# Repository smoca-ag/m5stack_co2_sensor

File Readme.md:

# Build your own portable, graphing CO₂ sensor

## Motivation

CO₂ levels measured indoors can be used as an indicator of air quality.

Outdoor air has a CO₂ ppm level of 400 ppm. Humans exhale air with 40000 ppm. You can calculate the percentage of exhaust air you are breathing by dividing measured CO₂ level above outdoor by the human exhaust level. Used air might contain aerosols which might contain the corona virus.

High indoor CO₂ levels also have an impact on the cognitive performance of humans.

Smoca AG decided to build this easy to reproduce CO₂ measuring device to help slow the spread of the corona virus in offices.
It supports its users in deciding when ventilating the room begin monitored is advisable. It also raises awareness for the correlation between CO₂ level and air quality.

## Hardware

The following hardware is needed:

| description                 | cost     | link                                                                                                                             |
| --------------------------- | -------- | -------------------------------------------------------------------------------------------------------------------------------- |
| Sensirion SCD30             | 54 USD   | https://www.digikey.com/en/products/detail/sensirion-ag/SCD30/8445334<br>Switzerland: https://www.bastelgarage.ch/co2-sensor-scd30-sensirion                                                            |
| M5 Stack Core2              | 39.9 USD | https://www.digikey.com/en/products/detail/m5stack-technology-co-ltd/K010/13151126?s=N4IgTCBcDaILYFYDOAXAhgYwNYAIMHsAnAUwgF0BfIA<br>Switzerland: https://www.bastelgarage.ch/m5stack-core2-esp32-iot-entwicklungs-kit |
| M5 Stack Proto Board        | 2.95 USD | https://www.digikey.com/en/products/detail/m5stack-technology-co-ltd/M001/10492145<br>Switzerland: https://www.bastelgarage.ch/m5stack-core-development-proto-board                                               |
| M5 Stack PLC Base           | 9.95 USD | https://m5stack.com/collections/m5-base/products/plc-proto-industrial-board-module<br>Switzerland: https://www.bastelgarage.ch/m5stack-plc-proto-base-industrial-board                                               |
| M5 Stack Battery (optional) | 7.95 USD | https://www.digikey.com/en/products/detail/m5stack-technology-co-ltd/M002/10492127<br>Switzerland: https://www.bastelgarage.ch/m5stack-battery-module-700mah-fur-esp32-core                                               |

Note: The optional battery increases the battery operation time from 6 to 10 hours.

### Building

|Description | Image
|----------- | -----------
|1. Power the Core2 module. A factory test application should be loaded. Test the device. |
|2. Remove the bottom of the Core2 module. Keep the battery there or replace it with the optional bigger one. | 
|3. Remove the PCB from the proto module. |
|4. Connect the SCD30 module to the proto module. We used pin headers. | 
|5. Connect VDD with 3V3, GND with GND, TX/SCL with pin 5 and RX/SDA with pin 2. The other pins don't need to be connected to the proto module. | 
|5. Screw the proto module to the PLC Base |
|6. Screw the PLC Base to the Core2 module | 
|7. HW Done, load the software |

## Software

To initialise the device do the following:

1. Install [Platformio IDE](https://platformio.org/platformio-ide) or [PlatformIO Core](https://docs.platformio.org/en/latest/core/installation.html) to use another IDE
2. Open the `co2-sensor` project folder
3. Flash the `main.cpp` script to your M5 Stack Core2 with `pio run -t upload --upload-port {your_device}`. You can see a list of your devices with `pio device list`. Dependencies are installed automatically.

## Features

#### Calibration

The SCD30 can be calibrated manually or automatically. For manual calibration, the device must be placed outdoors for at least five minutes. Then the calibration can be adjusted. Fresh air has a CO₂ concentration of about 400 ppm. To use automatic calibration, the device must have access to fresh air for at least one hour a day.

#### WiFi

To use MQTT, synchronization and update functionality the device must have internet connection. To add WiFi credentials the device opens an access point with a web interface (Default IP is 192.168.4.1). 

#### Data sharing via MQTT

[MQTT](https://mqtt.org/) can be used to send the sensors data to a custom MQTT broker. Server, Port, Topic, Device name, Username and Password can also be configured in the web interface. Each minute the device sends its data in the following format: `{TOPIC}/{CATEGORY} {VALUE}`. Here an example: `sensor/co2 650`.  
Topics are able to have subtopics: `office2/meeting_room1/co2 1100`.  
The following categories are provided by the device: `/co2`, `/humidity`, `/temperature`.

#### Time synchronization

To keep time up to date the device synchronizes with a time server each night between two and three o'clock.

#### Firmware updates

Is a new firmware available, it can manually be updated via WiFi.

#### SNMP

Using SNMP you are able to read the values of the co2, temperature and humidity sensors and also check the battery status of the device:
1. First you have to make sure you have net-snmp installed on your system. You can do this using your package manager or by downloading it from http://www.net-snmp.org/download.html
2. Second you have to find out where your mib files are stored using the command ```net-snmp-config --default-mibdirs```.
3. Then you have to copy the [mib file](./snmp-mib/sensorhub.mib) from ```/snmp-mib/sensorhub.mib``` into one of the listed directories. e.g. ```cp snmp-mib/sensorhub.mib ~/.snmp/mibs```
4. Done that, you can now use snmptable to list the sensors: 
    ```snmptable -m +SENSORHUB-MIB -c public {IP-Address} shSensorTable```
    \
    Which should output the following:
    ```
    SNMP table: SENSORHUB-MIB::shSensorTable

    shSensorName
            SCD30
            BATTERY
   ```
    or to list the measurement values: 
    ```snmptable -m +SENSORHUB-MIB -c public {IP-Address} shMeasurementTable```
    \
    Which should output something like this:
    ```
    SNMP table: SENSORHUB-MIB::shMeasurementTable

    shMeasurementType shMeasurementValue
                co2                  617
        temperature                  207
           humidity                  433
            voltage                  3
    electricCurrent                  276
   ```

## Usage

**Disclaimer This is not a safety device. Always follow the local regulations regarding corona safety. No warranty is provided**

### Graphs

- The graphs alway show the last six hours. Every line on the graph represents the measurement of one minute. The last value measured in the given minute is used for the graph.
- To switch between different graphs (temperature / humidity / battery / co2) touch the corresponding value in the display

### microsd

If a microsd card formated with fat is present, a csv file, data.txt will be written every 2 seconds with the timestamp, the co2 level, the humidity, the temperature and the current battery charge.

### CO₂

| level           | color  | description                                                                                               |
| --------------- | ------ | --------------------------------------------------------------------------------------------------------- |
| < 600 ppm       | blue   | outdoor air                                                                                               |
| 600 - 800 ppm   | green  | fresh indoor air                                                                                          |
| 800 - 1000 ppm  | yellow | indoor air, ventilate the room if possible, small possibility of virus transmission                       |
| 1000 - 1400 ppm | orange | used indoor air, ventilate the room, cognition is impacted, possibility of virus transmission             |
| > 1400 ppm      | red    | heavy used indoor air, heavy cognition impact, high possiblity of virus transmission, ventilation needed. |

## Extended uses (no code provided)

- We use it at our office to control a couple of exhaust / inlet pwm computer fans to keep the CO₂ level below 800 ppm.
- We log the measurement results to a influxdb with a grafana dashboard. The grafana instance sends alerts to telegram for CO₂ levels above 800 ppm.

## SCD4x
There is a PCB in the PCB folder for SCD41 Support. The Code Supports transparently SCD40 and SCD30 at the moment.

## Contact

If you have any suggestions for the project feel free to file an issue. If you want to build the device on a bigger scale / have any other development / prototyping needs, feel free to contact us: info@smoca.ch

## License

Copyright (c) 2020 David Gunzinger / smoca AG www.smoca.ch \
Code: GPL v3 \
Text / Graphics / Photographs: CC BY-SA

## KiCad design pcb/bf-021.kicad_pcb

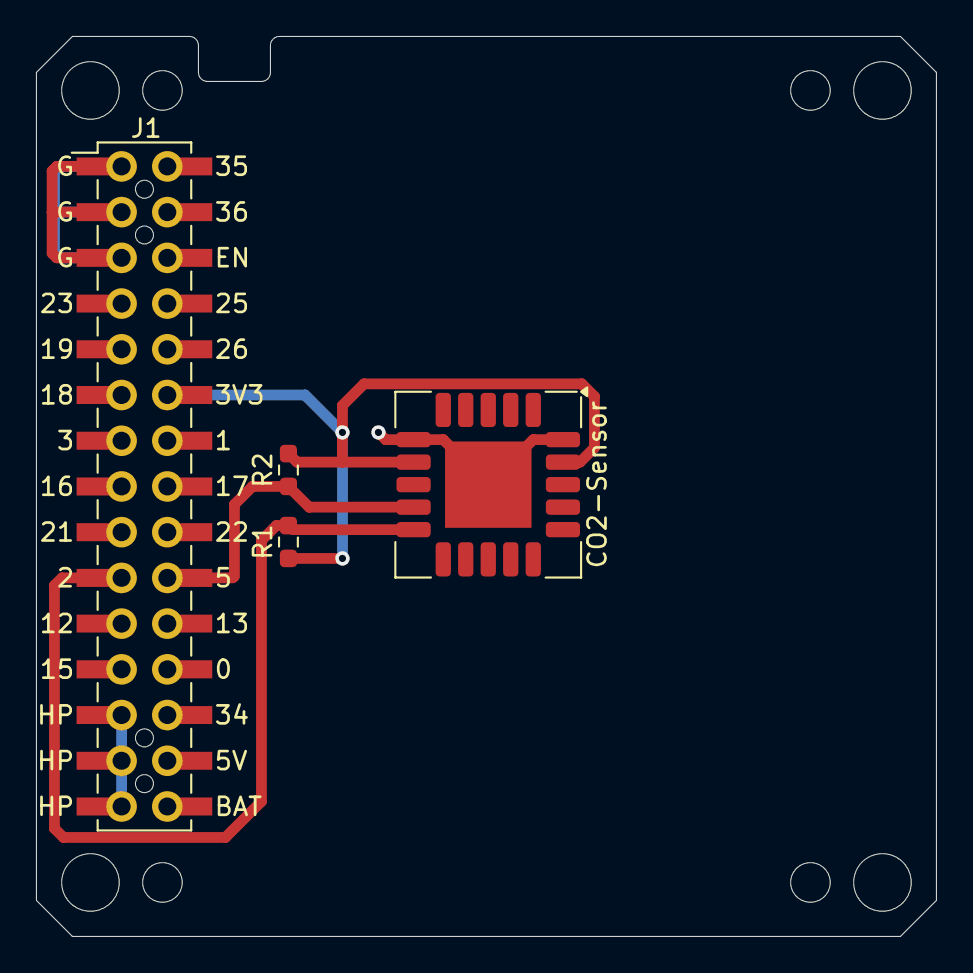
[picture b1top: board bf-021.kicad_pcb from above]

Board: 2 copper layers, 50.0 x 50.0 mm, 12 parts (0 on the bottom side), 4 nets.

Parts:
CO2-Sensor: SCD40-D-R2; Sensirion_SCD4x-1EP_10.1x10.1mm_P1.25mm_EP4.8x4.8mm
H1, H2, H3, H4: MountingHole; BF@MountingHole_3.2mm_M3
H5, H6, H7, H8: MountingHole; BF@MountingHole_2.2mm_M2
J1: M-BUS; BF@M5Stack_MBUS
R1, R2: 10k; R_0603_1608Metric_Pad0.98x0.95mm_HandSolder

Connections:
+3V3: CO2-Sensor.7 (VDD), CO2-Sensor.19 (VDD), J1.11, R1.1, R2.2
GND: CO2-Sensor.6 (GND), CO2-Sensor.20 (GND), CO2-Sensor.21 (GND), J1.2, J1.4, J1.6
SDA: CO2-Sensor.9 (SCL), CO2-Sensor.10 (SDA), J1.19, J1.20, R1.2, R2.1
VBUS: J1.26, J1.28, J1.30

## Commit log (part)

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2020-10-15 initial for github
2020-10-15 images?
2020-10-15 line breaks
2020-10-16 added company url / extended ussage
2020-10-16 inital flyer commit
2020-10-16 line breaks in License
2020-10-18 5.5 temperature offset
2020-10-20 flyer update
2020-10-20 exhale air has 40000 ppm
2020-10-20 added german flyer
2020-10-21 comment about esp32 development version
2020-11-11 readme update
2020-12-11 update to latest libraries and core
2021-01-04 calibration
2021-01-04 turned event based into state based
2021-01-04 draw graph after menu switch
2021-01-04 set min and max for forced calibration
2021-01-04 showing current co2 offset in calibration menu
2021-01-05 added logo
2021-01-05 auto calibration is now saved in a file
2021-01-06 added persistent state for battery and calibration
2021-01-08 (WIP) implemented AP to get wifi creds
2021-01-12 Added WiFi UI, updated Buttons
2021-01-12 fixed reset and ui
2021-01-12 fixed ui for resetting wifi
2021-01-12 fixed shown wifi info
2021-01-13 added functions
2021-01-13 refactored color constants
2021-01-13 wifi has random password, updated nav
2021-01-13 fixed connection: 0
2021-01-13 fixed ui
2021-01-15 refactored WiFi
2021-01-15 removed useless method
2021-01-15 fixed reboot bug
2021-01-15 wifi bug fix
2021-01-15 finally fixed connection 0
2021-01-15 fixed UI bug
2021-01-15 refactored
2021-01-15 added setRtc function
2021-01-15 updated library links
2021-01-15 removed setRtc
2021-01-15 added versions to libraries
2021-01-18 added time sync functions
2021-01-18 added time ui
2021-01-18 removed rtc folder
2021-01-18 removed old project files
2021-01-18 added platformio project
2021-01-18 added method declarations
2021-01-18 removed redundant dependencies
2021-01-18 fix some compile errors
2021-01-18 added headers
2021-01-18 fix compilation
2021-01-19 some auto format
2021-01-19 added .idea to gitignore
2021-01-19 clion auto format
2021-01-19 improved calibration UI
2021-01-19 removed upload-port
2021-01-19 fixed WiFi ui
2021-01-20 added case
2021-01-20 added amf
2021-01-20 added header file
2021-01-20 added update UI
2021-01-20 added method to fetch version.json from server
2021-01-20 added update handler
2021-01-20 fixed some bugs
2021-01-21 fixed state and ui bugs
2021-01-21 fixed update bug
2021-01-21 fixed sync bug
2021-01-21 fixed ui bugs
2021-01-21 cleaned up function
2021-01-21 bypassed button bug
2021-01-21 ecansing version 3
2021-01-21 m5 edges
2021-01-21 added mqtt feature
2021-01-22 changed mqtt lib
2021-01-22 fixed wifi client bug
2021-01-22 remove center screw
2021-01-22 improved code
2021-01-22 added mqtt ui
2021-01-22 mqtt ui
2021-01-22 dont use mqtt if variables are empty
2021-01-22 next try at a nice case
2021-01-23 edge for magnet
2021-01-24 updated encasing
2021-01-25 fixed mqtt connection bug
2021-01-25 added configurable topic
2021-01-25 fixed guru meditation error
2021-01-25 fixed memory bugs
2021-01-25 fixed not connecting to mqtt after reboot
2021-01-25 cleaned up code
2021-01-26 moved struct/enum into header file
2021-01-26 renamed function
2021-01-26 refactored code
2021-01-26 fixed disgruence of ui and state
2021-01-26 refactored wifi manager
2021-01-26 Fixed timeout
2021-01-27 fixed bug
2021-01-27 added home button
2021-01-27 fixed some issues
2021-01-27 removed redundant code
2021-01-28 fixed config portal bug
2021-01-28 fixed password and exit issue
2021-01-28 now resetting all SSIDs
2021-01-28 now shows AP creds after wifi is turned on the first time
2021-01-29 fix some nasty error messages
2021-01-29 strings should be compared with strncmp
2021-01-29 reenable mqtt loop
2021-01-29 set sane baud rate
2021-01-29 increased version number
2021-01-29 time sync now considers timezones
2021-01-29 now saves mqtt config
2021-01-29 increased patch
2021-01-29 fixed table
2021-01-29 fixed wrong access point starts
2021-02-01 device name now changes after a reset
2021-02-01 added state machine to avoid blocking while connecting to wifi
2021-02-02 fixed timing in state machine
2021-02-02 moved updateWiFiState
2021-02-02 font
2021-02-02 refactored state machine (WIP)
2021-02-02 reformat some stuff
2021-02-03 stuff
2021-02-03 can now connect to wifi
2021-02-03 fixed config portal bugs
2021-02-03 wifi scan is not blocking anymore
2021-02-03 somehow improved blocking time for starting config portal
2021-02-04 fixed blocking
2021-02-04 fixes
2021-02-05 not using fork
2021-02-09 added stl for case
2021-03-02 turn off wifi completely
2021-04-17 rtcsync loop fixed
2021-04-19 set timeout for getLocalTime
2021-04-19 increased version
2021-08-12 Add links to Bastelgarage
    Fixes #5 from @tobru
2021-08-24 updated M5Core2 to newest version
2021-08-24 added rotation settings
2021-08-24 format
2021-08-24 fixed calibration title
2021-11-02 initial snmp support
2021-11-03 added custom mib
2021-11-05 wip snmp
2021-11-08 snmp works
2021-11-08 refactor
2021-11-16 updated mib file
2021-11-17 added snmp usage to README
2021-11-25 Fix M5Core2 library declaration
2022-01-05 added de manual
2022-01-05 updated platform io to work with newer versions, see github
2022-01-05 fixed rtc and removed unused dependencies
2022-01-05 updated version
2022-01-05 fix wifi on / off button
2022-01-05 fix random ssid
2022-01-05 allow wifi off always
2022-01-06 update pdfs to remove badges
2022-01-06 added old image without badge
2022-01-06 added default return value to C function
2022-01-06 fixed password to be always saved as 1 in state
2022-01-06 abort configuration when wifi is turned off while configuration is running
2022-08-22 added battery persentage to mqtt
2022-08-22 add battery mqtt to readme
2022-12-23 Add homeassistant mqtt discovery feature
2022-12-23 Set RETAIN flag to true when publishing discovery configurations
2022-12-23 Fix type errors in mqtt.publish
2022-12-28 Change usage of Arduino strings to char inside config structs
2022-12-29 Change strncpy to strlcpy; increase size of unique id char arrays
2022-12-30 Replace strncpy/strcpy with strlcpy
2022-12-30 Replace direct call of strlcpy with dynamic size macro
2023-03-02 Add state_class to discovery topics
2023-03-12 Reduce overhead of measurement c_strings
2023-03-22 Remove DISCOVERY_STATE_CLASS_LEN directive
2024-05-31 smal fixes
2024-06-03 added custom pcb design
2024-06-04 update librarys
2024-06-04 check which sensor
2024-06-04 improved design
2024-06-04 fix crash
2024-06-04 upload fixed
2024-06-04 update library versions
2024-06-04 partitions table
2024-06-04 factor 10 for temp and humidity
2024-06-05 temp offset
2024-06-19 fixed connector being on wrong side
2024-07-02 base encasing4
2024-07-02 holes for screws
2024-07-02 cut grid
2024-07-02 stl file
2024-07-03 schraubengewinde, magnetanpassung
2024-07-04 magnetloch tiefer
2024-07-17 temp calib settings
2024-07-19 computing new temp_offset
2025-05-28 compile still broken, but will fix later
2025-05-28 updated snmp, still broken

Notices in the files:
pcb/bf-021.kicad_pcb:
Copyright 2022 BotanicFields, Inc.
